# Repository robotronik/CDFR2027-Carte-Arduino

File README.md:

# CDFR2027-Carte-Arduino
La carte Arduino Controle de moteur pour CDFR 2027

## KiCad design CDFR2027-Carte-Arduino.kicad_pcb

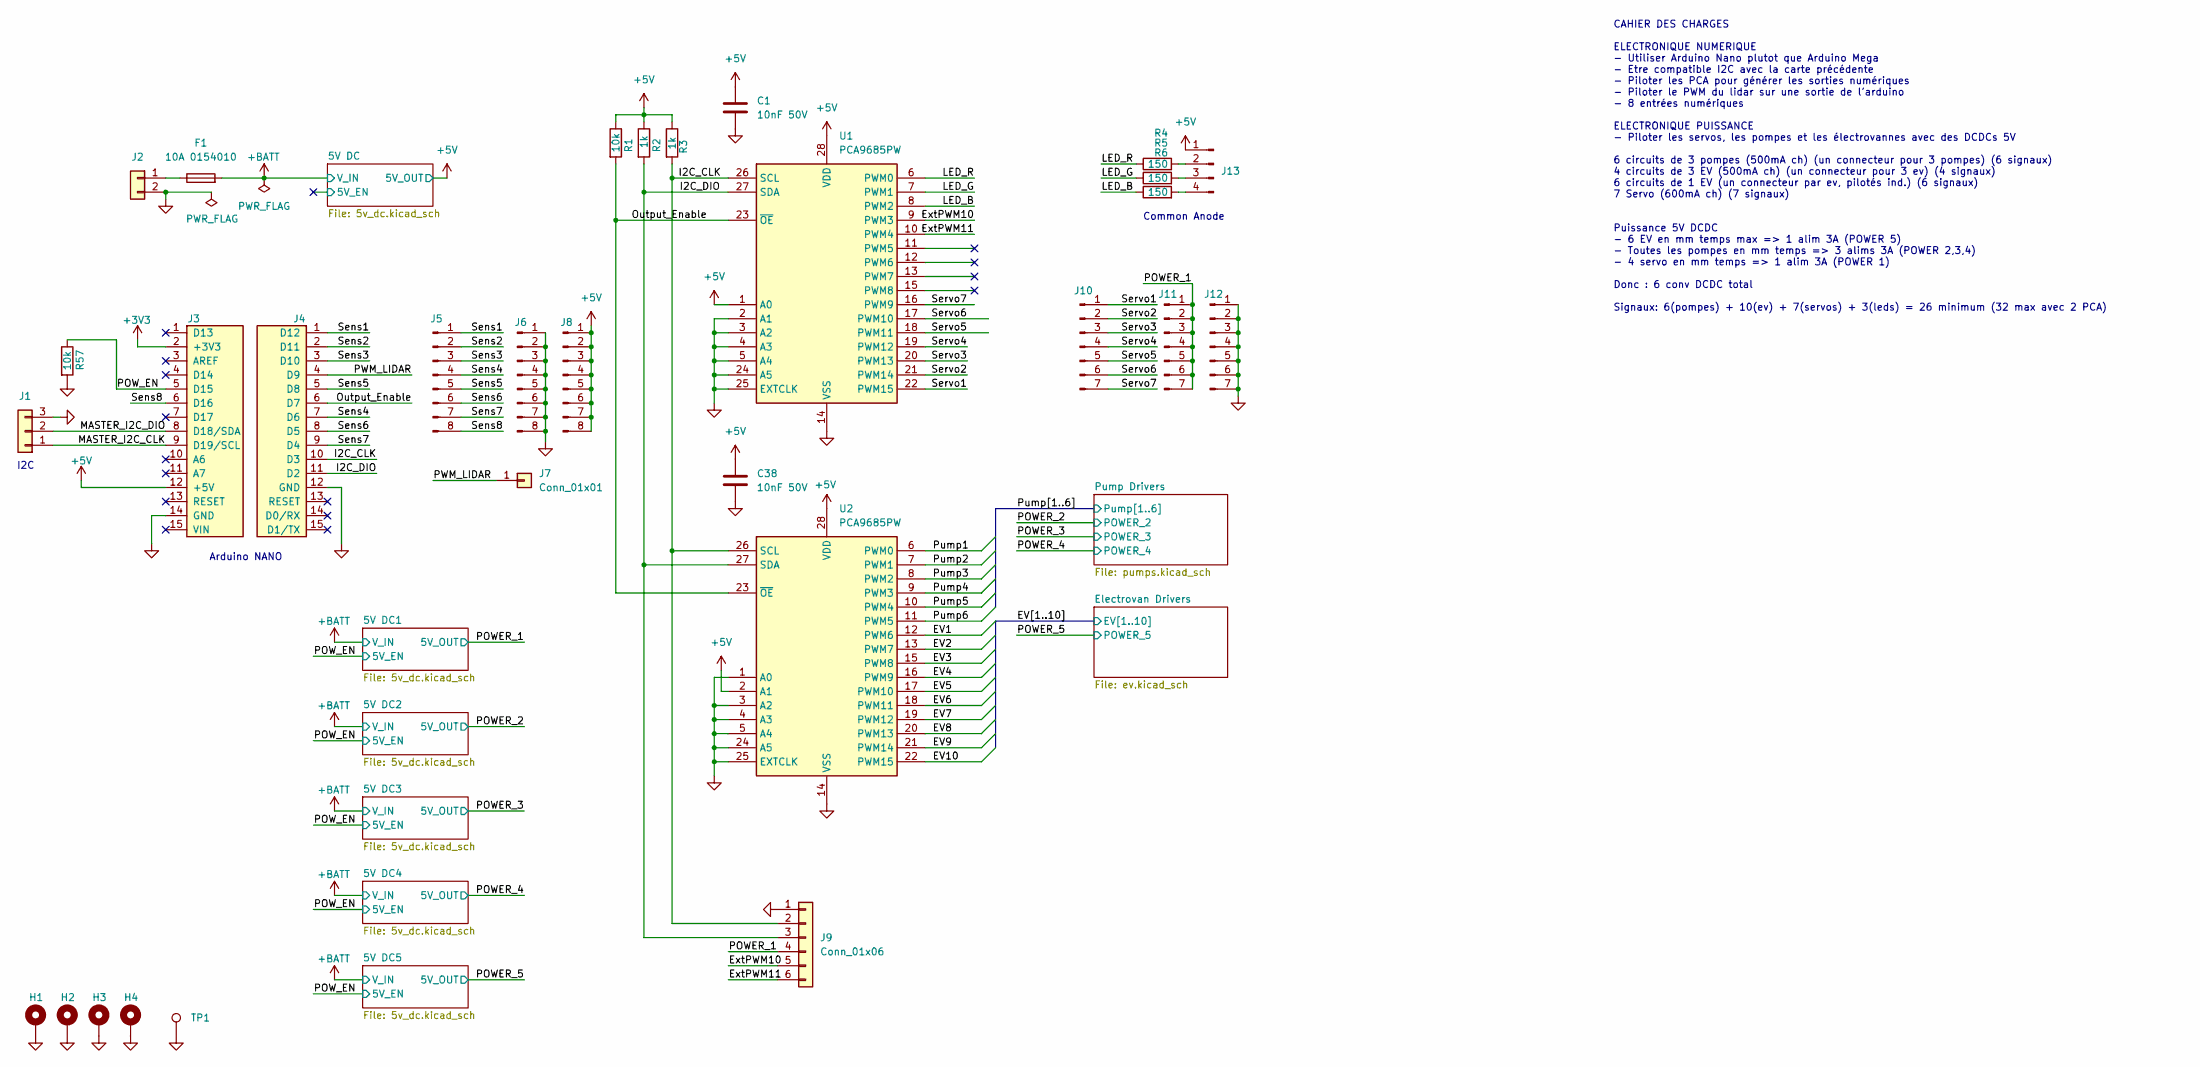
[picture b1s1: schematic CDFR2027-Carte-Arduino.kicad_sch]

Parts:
C1, C38: 10nF 50V; C_0805_2012Metric_Pad1.18x1.45mm_HandSolder; JLCPCB Part # C1710
F1: 10A 0154010; FUSE_0154004.DR; JLCPCB Part # C206921
H1, H2, H3, H4: MountingHole_Pad; MountingHole_3.2mm_M3_Pad_Via
J1: Conn_01x03; JST_XH_B3B-XH-A_1x03_P2.50mm_Vertical
J2: Conn_01x02; CUI_TBP01R1-508-02BE
J3: Analog; PinHeader_1x15_P2.54mm_Vertical
J4: Digital; PinHeader_1x15_P2.54mm_Vertical
J5, J6, J8: Conn_01x08_Pin; PinHeader_1x08_P2.54mm_Vertical
J7: Conn_01x01; PinHeader_1x01_P2.54mm_Vertical
J9: Conn_01x06; PinHeader_1x06_P2.54mm_Vertical
J10, J11, J12: Conn_01x07_Pin; PinHeader_1x07_P2.54mm_Vertical
J13: Conn_01x04_Pin; PinHeader_1x04_P2.54mm_Vertical
R1, R57: 10k; R_0805_2012Metric_Pad1.20x1.40mm_HandSolder; JLCPCB Part # C17414
R2, R3: 1k; R_0805_2012Metric_Pad1.20x1.40mm_HandSolder; JLCPCB Part # C17513
R4, R5, R6: 150; R_0805_2012Metric_Pad1.20x1.40mm_HandSolder; JLCPCB Part # C17471
TP1: TestPoint; TestPoint_Bridge_Pitch2.0mm_Drill0.7mm
U1, U2: PCA9685PW; TSSOP-28_4.4x9.7mm_P0.65mm; JLCPCB Part # C2678753

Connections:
+3V3: J3.2 (+3V3)
+5V: C1.1, C38.1, J3.12 (+5V), J8.1, J8.2, J8.3, J8.4, J8.5, J8.6, J8.7, J8.8, J13.1, R1.1, R2.1, R3.1, U1.1 (A0), U1.28 (VDD), U2.2 (A1), U2.28 (VDD); also elsewhere on the board
+BATT: F1.2; also elsewhere on the board
/EV1: U2.12 (PWM6); also elsewhere on the board
/EV2: U2.13 (PWM7); also elsewhere on the board
/EV3: U2.15 (PWM8); also elsewhere on the board
/EV4: U2.16 (PWM9); also elsewhere on the board
/EV5: U2.17 (PWM10); also elsewhere on the board
/EV6: U2.18 (PWM11); also elsewhere on the board
/EV7: U2.19 (PWM12); also elsewhere on the board
/EV8: U2.20 (PWM13); also elsewhere on the board
/EV9: U2.21 (PWM14); also elsewhere on the board
/EV10: U2.22 (PWM15); also elsewhere on the board
/ExtPWM10: J9.5, U1.9 (PWM3)
/ExtPWM11: J9.6, U1.10 (PWM4)
/I2C_CLK: J4.10 (D3), J9.2, R3.2, U1.26 (SCL), U2.26 (SCL)
/I2C_DIO: J4.11 (D2), J9.3, R2.2, U1.27 (SDA), U2.27 (SDA)
/LED_B: R6.1, U1.8 (PWM2)
/LED_G: R5.1, U1.7 (PWM1)
/LED_R: R4.1, U1.6 (PWM0)
/MASTER_I2C_CLK: J1.1, J3.9 (D19/SCL)
/MASTER_I2C_DIO: J1.2, J3.8 (D18/SDA)
/Output_Enable: J4.6 (D7), R1.2, U1.23 (~OE), U2.23 (~OE)
/POWER_1: J9.4, J11.1, J11.2, J11.3, J11.4, J11.5, J11.6, J11.7; also elsewhere on the board
/POW_EN: J3.5 (D15), R57.1; also elsewhere on the board
/PWM_LIDAR: J4.4 (D9), J7.1 (Pin_1_1)
/Pump1: U2.6 (PWM0); also elsewhere on the board
/Pump2: U2.7 (PWM1); also elsewhere on the board
/Pump3: U2.8 (PWM2); also elsewhere on the board
/Pump4: U2.9 (PWM3); also elsewhere on the board
/Pump5: U2.10 (PWM4); also elsewhere on the board
/Pump6: U2.11 (PWM5); also elsewhere on the board
/Sens1: J4.1 (D12), J5.1
/Sens2: J4.2 (D11), J5.2
/Sens3: J4.3 (D10), J5.3
/Sens4: J4.7 (D6), J5.4
/Sens5: J4.5 (D8), J5.5
/Sens6: J4.8 (D5), J5.6
/Sens7: J4.9 (D4), J5.7
/Sens8: J3.6 (D16), J5.8
/Servo1: J10.1, U1.22 (PWM15)
/Servo2: J10.2, U1.21 (PWM14)
/Servo3: J10.3, U1.20 (PWM13)
/Servo4: J10.4, U1.19 (PWM12)
/Servo5: J10.5, U1.18 (PWM11)
/Servo6: J10.6, U1.17 (PWM10)
/Servo7: J10.7, U1.16 (PWM9)
GND: C1.2, C38.2, H1.1 (1_1), H2.1 (1_1), H3.1 (1_1), H4.1 (1_1), J1.3, J2.2, J3.14 (GND), J4.12 (GND), J6.1, J6.2, J6.3, J6.4, J6.5, J6.6, J6.7, J6.8, J9.1, J12.1, J12.2, J12.3, J12.4, J12.5, J12.6, J12.7, R57.2, TP1.1 (1_1), U1.2 (A1), U1.3 (A2), U1.4 (A3), U1.5 (A4), U1.14 (VSS), U1.24 (A5), U1.25 (EXTCLK), U2.1 (A0), U2.3 (A2), U2.4 (A3), U2.5 (A4), U2.14 (VSS), U2.24 (A5), U2.25 (EXTCLK); also elsewhere on the board
unnamed: F1.1, J2.1
unnamed: J13.2, R4.2
unnamed: J13.3, R5.2
unnamed: J13.4, R6.2

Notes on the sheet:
I2C
Arduino NANO
Common Anode
CAHIER DES CHARGES ELECTRONIQUE NUMERIQUE - Utiliser Arduino Nano plutot que Arduino Mega - Etre compatible I2C avec la carte précédente - Piloter les PCA pour générer les sorties numériques - Piloter le PWM du lidar sur une sortie de l'arduino - 8 entrées numériques ELECTRONIQUE PUISSANCE - Pilote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

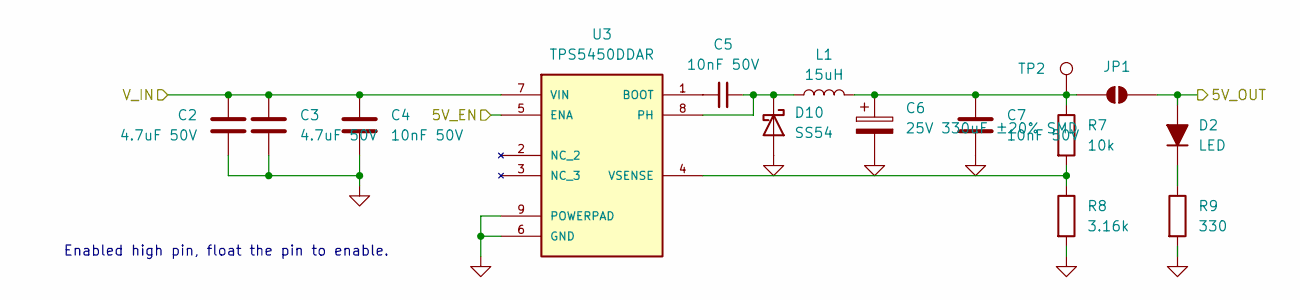
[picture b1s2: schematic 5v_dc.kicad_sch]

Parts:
C2, C3: 4.7uF 50V; C_0805_2012Metric_Pad1.18x1.45mm_HandSolder; JLCPCB Part # C437557
C4, C5, C7: 10nF 50V; C_0805_2012Metric_Pad1.18x1.45mm_HandSolder; JLCPCB Part # C1710
C6: 25V 330uF ±20% SMD; CP_Elec_8x10; JLCPCB Part # C127884
D2: LED; D_0805_2012Metric_Pad1.15x1.40mm_HandSolder; JLCPCB Part # C2297
D10: SS54; D_SMA; JLCPCB Part # C22452
JP1: SolderJumper_2_Open; SolderJumper-2_P1.3mm_Open_RoundedPad1.0x1.5mm
L1: 15uH; L_12x12mm_H8mm; JLCPCB Part # C40000
R7: 10k; R_0805_2012Metric_Pad1.20x1.40mm_HandSolder; JLCPCB Part # C17414
R8: 3.16k; R_0805_2012Metric_Pad1.20x1.40mm_HandSolder; JLCPCB Part # C2933413
R9: 330; R_0805_2012Metric_Pad1.20x1.40mm_HandSolder; JLCPCB Part # C17630
TP2: TestPoint; TestPoint_THTPad_D2.0mm_Drill1.0mm
U3: TPS5450DDAR; CONV_TPS5450DDAR; JLCPCB Part # C114425

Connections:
+5V: D2.2 (A), JP1.2 (B); also elsewhere on the board
+BATT: C2.2, C3.1, C4.1, U3.7 (VIN); also elsewhere on the board
/5V DC/5V_EN: U3.5 (ENA)
GND: C2.1, C3.2, C4.2, C6.2, C7.2, D10.2 (A), R8.2, R9.2, U3.6 (GND), U3.9 (POWERPAD); also elsewhere on the board
unnamed: D2.1 (K), R9.1
unnamed: C5.2, D10.1 (K), L1.1, U3.8 (PH)
unnamed: C6.1, C7.1, JP1.1 (A), L1.2, R7.1, TP2.1 (1_1)
unnamed: C5.1, U3.1 (BOOT)
unnamed: R7.2, R8.1, U3.4 (VSENSE)

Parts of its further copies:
C8, C9, C14, C15, C20, C21, C26, C27, C32, C33: 4.7uF 50V; C_0805_2012Metric_Pad1.18x1.45mm_HandSolder; JLCPCB Part # C437557
C10, C11, C13, C16, C17, C19, C22, C23, C25, C28, C29, C31, C34, C35, C37: 10nF 50V; C_0805_2012Metric_Pad1.18x1.45mm_HandSolder; JLCPCB Part # C1710
C12, C18, C24, C30, C36: 25V 330uF ±20% SMD; CP_Elec_8x10; JLCPCB Part # C127884
D4, D6, D8, D11, D13: LED; D_0805_2012Metric_Pad1.15x1.40mm_HandSolder; JLCPCB Part # C2297
D12, D29, D30, D31, D32: SS54; D_SMA; JLCPCB Part # C22452
JP2, JP3, JP4, JP5, JP6: SolderJumper_2_Open; SolderJumper-2_P1.3mm_Open_RoundedPad1.0x1.5mm
L2, L3, L4, L5, L6: 15uH; L_12x12mm_H8mm; JLCPCB Part # C40000
R10, R13, R16, R21, R24: 10k; R_0805_2012Metric_Pad1.20x1.40mm_HandSolder; JLCPCB Part # C17414
R11, R14, R17, R22, R25: 3.16k; R_0805_2012Metric_Pad1.20x1.40mm_HandSolder; JLCPCB Part # C2933413
R12, R15, R18, R23, R26: 330; R_0805_2012Metric_Pad1.20x1.40mm_HandSolder; JLCPCB Part # C17630
TP3, TP4, TP5, TP6, TP7: TestPoint; TestPoint_THTPad_D2.0mm_Drill1.0mm
U4, U5, U6, U7, U8: TPS5450DDAR; CONV_TPS5450DDAR; JLCPCB Part # C114425

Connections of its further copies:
+BATT: C8.2, C9.1, C10.1, C14.2, C15.1, C16.1, C20.2, C21.1, C22.1, C26.2, C27.1, C28.1, C32.2, C33.1, C34.1, U4.7 (VIN), U5.7 (VIN), U6.7 (VIN), U7.7 (VIN), U8.7 (VIN); also elsewhere on the board
/POWER_1: D4.2 (A), JP2.2 (B); also elsewhere on the board
/POWER_2: D6.2 (A), JP3.2 (B); also elsewhere on the board
/POWER_3: D8.2 (A), JP4.2 (B); also elsewhere on the board
/POWER_4: D11.2 (A), JP5.2 (B); also elsewhere on the board
/POWER_5: D13.2 (A), JP6.2 (B); also elsewhere on the board
/POW_EN: U4.5 (ENA), U5.5 (ENA), U6.5 (ENA), U7.5 (ENA), U8.5 (ENA); also elsewhere on the board
GND: C8.1, C9.2, C10.2, C12.2, C13.2, C14.1, C15.2, C16.2, C18.2, C19.2, C20.1, C21.2, C22.2, C24.2, C25.2, C26.1, C27.2, C28.2, C30.2, C31.2, C32.1, C33.2, C34.2, C36.2, C37.2, D12.2 (A), D29.2 (A), D30.2 (A), D31.2 (A), D32.2 (A), R11.2, R12.2, R14.2, R15.2, R17.2, R18.2, R22.2, R23.2, R25.2, R26.2, U4.6 (GND), U4.9 (POWERPAD), U5.6 (GND), U5.9 (POWERPAD), U6.6 (GND), U6.9 (POWERPAD), U7.6 (GND), U7.9 (POWERPAD), U8.6 (GND), U8.9 (POWERPAD); also elsewhere on the board
unnamed: D4.1 (K), R12.1
unnamed: D6.1 (K), R15.1
unnamed: D8.1 (K), R18.1
unnamed: D11.1 (K), R23.1
unnamed: C11.2, D12.1 (K), L2.1, U4.8 (PH)
unnamed: D13.1 (K), R26.1
unnamed: C17.2, D29.1 (K), L3.1, U5.8 (PH)
unnamed: C23.2, D30.1 (K), L4.1, U6.8 (PH)
unnamed: C29.2, D31.1 (K), L5.1, U7.8 (PH)
unnamed: C35.2, D32.1 (K), L6.1, U8.8 (PH)
unnamed: C12.1, C13.1, JP2.1 (A), L2.2, R10.1, TP3.1 (1_1)
unnamed: C18.1, C19.1, JP3.1 (A), L3.2, R13.1, TP4.1 (1_1)
unnamed: C24.1, C25.1, JP4.1 (A), L4.2, R16.1, TP5.1 (1_1)
unnamed: C30.1, C31.1, JP5.1 (A), L5.2, R21.1, TP6.1 (1_1)
unnamed: C36.1, C37.1, JP6.1 (A), L6.2, R24.1, TP7.1 (1_1)
unnamed: C11.1, U4.1 (BOOT)
unnamed: R10.2, R11.1, U4.4 (VSENSE)
unnamed: C17.1, U5.1 (BOOT)
unnamed: R13.2, R14.1, U5.4 (VSENSE)
unnamed: C23.1, U6.1 (BOOT)
unnamed: R16.2, R17.1, U6.4 (VSENSE)
unnamed: C29.1, U7.1 (BOOT)
unnamed: R21.2, R22.1, U7.4 (VSENSE)
unnamed: C35.1, U8.1 (BOOT)
unnamed: R24.2, R25.1, U8.4 (VSENSE)

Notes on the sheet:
Enabled high pin, float the pin to enable.

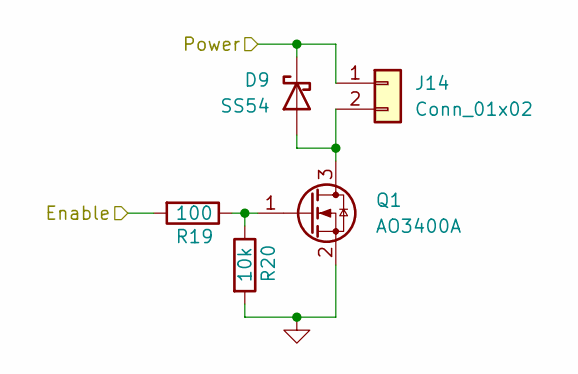
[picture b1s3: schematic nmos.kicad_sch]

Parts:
D9: SS54; D_SMA; JLCPCB Part # C22452
J14: Conn_01x02; JST_XH_B2B-XH-A_1x02_P2.50mm_Vertical
Q1: AO3400A; SOT-23; JLCPCB Part # C20917
R19: 100; R_0805_2012Metric_Pad1.20x1.40mm_HandSolder; JLCPCB Part # C17408
R20: 10k; R_0805_2012Metric_Pad1.20x1.40mm_HandSolder; JLCPCB Part # C17414

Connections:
/POWER_2: D9.1 (K), J14.1; also elsewhere on the board
/Pump1: R19.2; also elsewhere on the board
GND: Q1.2 (S), R20.2; also elsewhere on the board
unnamed: D9.2 (A), J14.2, Q1.3 (D)
unnamed: Q1.1 (G), R19.1, R20.1

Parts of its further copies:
D14, D15, D16, D17, D18, D19, D20, D21, D22, D23, D24, D25, D26, D27, D28: SS54; D_SMA; JLCPCB Part # C22452
J15, J16, J17, J18, J19, J20, J21, J22, J23, J24, J25, J26, J27, J28, J29: Conn_01x02; JST_XH_B2B-XH-A_1x02_P2.50mm_Vertical
Q2, Q3, Q4, Q5, Q6, Q7, Q8, Q9, Q10, Q11, Q12, Q13, Q14, Q15, Q16: AO3400A; SOT-23; JLCPCB Part # C20917
R27, R29, R31, R33, R35, R37, R39, R41, R43, R45, R47, R49, R51, R53, R55: 100; R_0805_2012Metric_Pad1.20x1.40mm_HandSolder; JLCPCB Part # C17408
R28, R30, R32, R34, R36, R38, R40, R42, R44, R46, R48, R50, R52, R54, R56: 10k; R_0805_2012Metric_Pad1.20x1.40mm_HandSolder; JLCPCB Part # C17414

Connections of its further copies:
/EV1: R37.2; also elsewhere on the board
/EV2: R39.2; also elsewhere on the board
/EV3: R41.2; also elsewhere on the board
/EV4: R43.2; also elsewhere on the board
/EV5: R45.2; also elsewhere on the board
/EV6: R47.2; also elsewhere on the board
/EV7: R49.2; also elsewhere on the board
/EV8: R51.2; also elsewhere on the board
/EV9: R53.2; also elsewhere on the board
/EV10: R55.2; also elsewhere on the board
/POWER_2: D14.1 (K), J15.1; also elsewhere on the board
/POWER_3: D15.1 (K), D16.1 (K), J16.1, J17.1; also elsewhere on the board
/POWER_4: D17.1 (K), D18.1 (K), J18.1, J19.1; also elsewhere on the board
/POWER_5: D19.1 (K), D20.1 (K), D21.1 (K), D22.1 (K), D23.1 (K), D24.1 (K), D25.1 (K), D26.1 (K), D27.1 (K), D28.1 (K), J20.1, J21.1, J22.1, J23.1, J24.1, J25.1, J26.1, J27.1, J28.1, J29.1; also elsewhere on the board
/Pump2: R27.2; also elsewhere on the board
/Pump3: R29.2; also elsewhere on the board
/Pump4: R31.2; also elsewhere on the board
/Pump5: R33.2; also elsewhere on the board
/Pump6: R35.2; also elsewhere on the board
GND: Q2.2 (S), Q3.2 (S), Q4.2 (S), Q5.2 (S), Q6.2 (S), Q7.2 (S), Q8.2 (S), Q9.2 (S), Q10.2 (S), Q11.2 (S), Q12.2 (S), Q13.2 (S), Q14.2 (S), Q15.2 (S), Q16.2 (S), R28.2, R30.2, R32.2, R34.2, R36.2, R38.2, R40.2, R42.2, R44.2, R46.2, R48.2, R50.2, R52.2, R54.2, R56.2; also elsewhere on the board
unnamed: D14.2 (A), J15.2, Q2.3 (D)
unnamed: D15.2 (A), J16.2, Q3.3 (D)
unnamed: D16.2 (A), J17.2, Q4.3 (D)
unnamed: D17.2 (A), J18.2, Q5.3 (D)
unnamed: D18.2 (A), J19.2, Q6.3 (D)
unnamed: D19.2 (A), J20.2, Q7.3 (D)
unnamed: D20.2 (A), J21.2, Q8.3 (D)
unnamed: D21.2 (A), J22.2, Q9.3 (D)
unnamed: D22.2 (A), J23.2, Q10.3 (D)
unnamed: D23.2 (A), J24.2, Q11.3 (D)
unnamed: D24.2 (A), J25.2, Q12.3 (D)
unnamed: D25.2 (A), J26.2, Q13.3 (D)
unnamed: D26.2 (A), J27.2, Q14.3 (D)
unnamed: D27.2 (A), J28.2, Q15.3 (D)
unnamed: D28.2 (A), J29.2, Q16.3 (D)
unnamed: Q2.1 (G), R27.1, R28.1
unnamed: Q3.1 (G), R29.1, R30.1
unnamed: Q4.1 (G), R31.1, R32.1
unnamed: Q5.1 (G), R33.1, R34.1
unnamed: Q6.1 (G), R35.1, R36.1
unnamed: Q7.1 (G), R37.1, R38.1
unnamed: Q8.1 (G), R39.1, R40.1
unnamed: Q9.1 (G), R41.1, R42.1
unnamed: Q10.1 (G), R43.1, R44.1
unnamed: Q11.1 (G), R45.1, R46.1
unnamed: Q12.1 (G), R47.1, R48.1
unnamed: Q13.1 (G), R49.1, R50.1
unnamed: Q14.1 (G), R51.1, R52.1
unnamed: Q15.1 (G), R53.1, R54.1
unnamed: Q16.1 (G), R55.1, R56.1

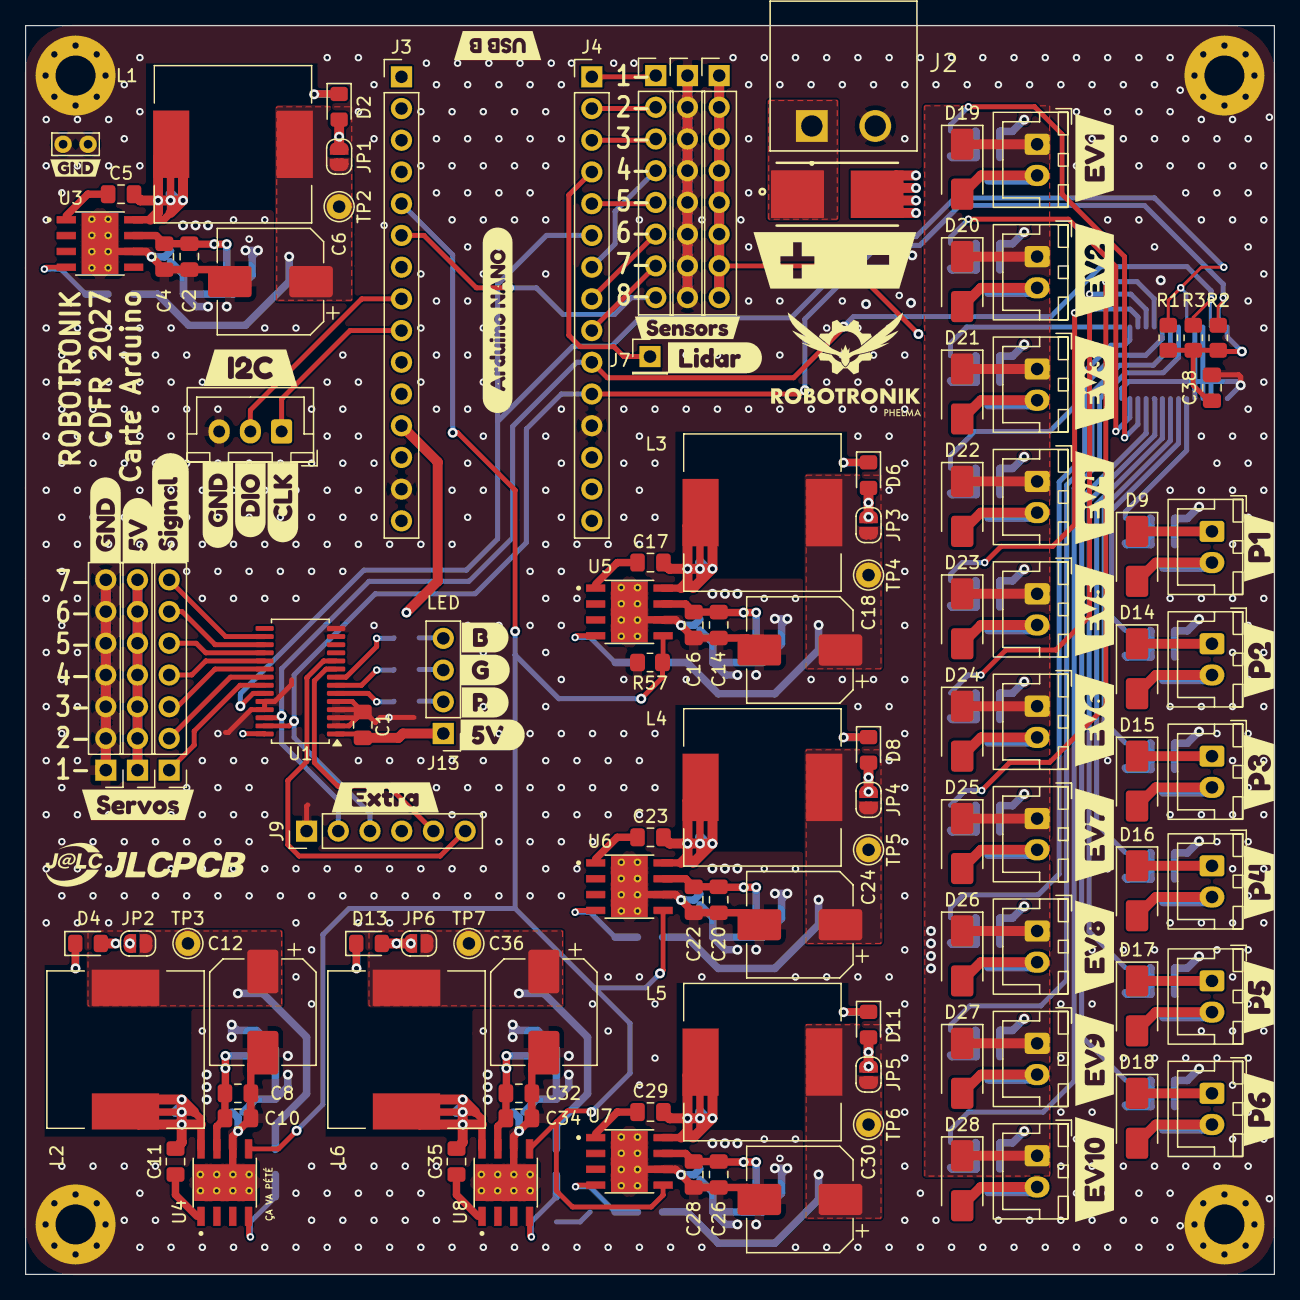
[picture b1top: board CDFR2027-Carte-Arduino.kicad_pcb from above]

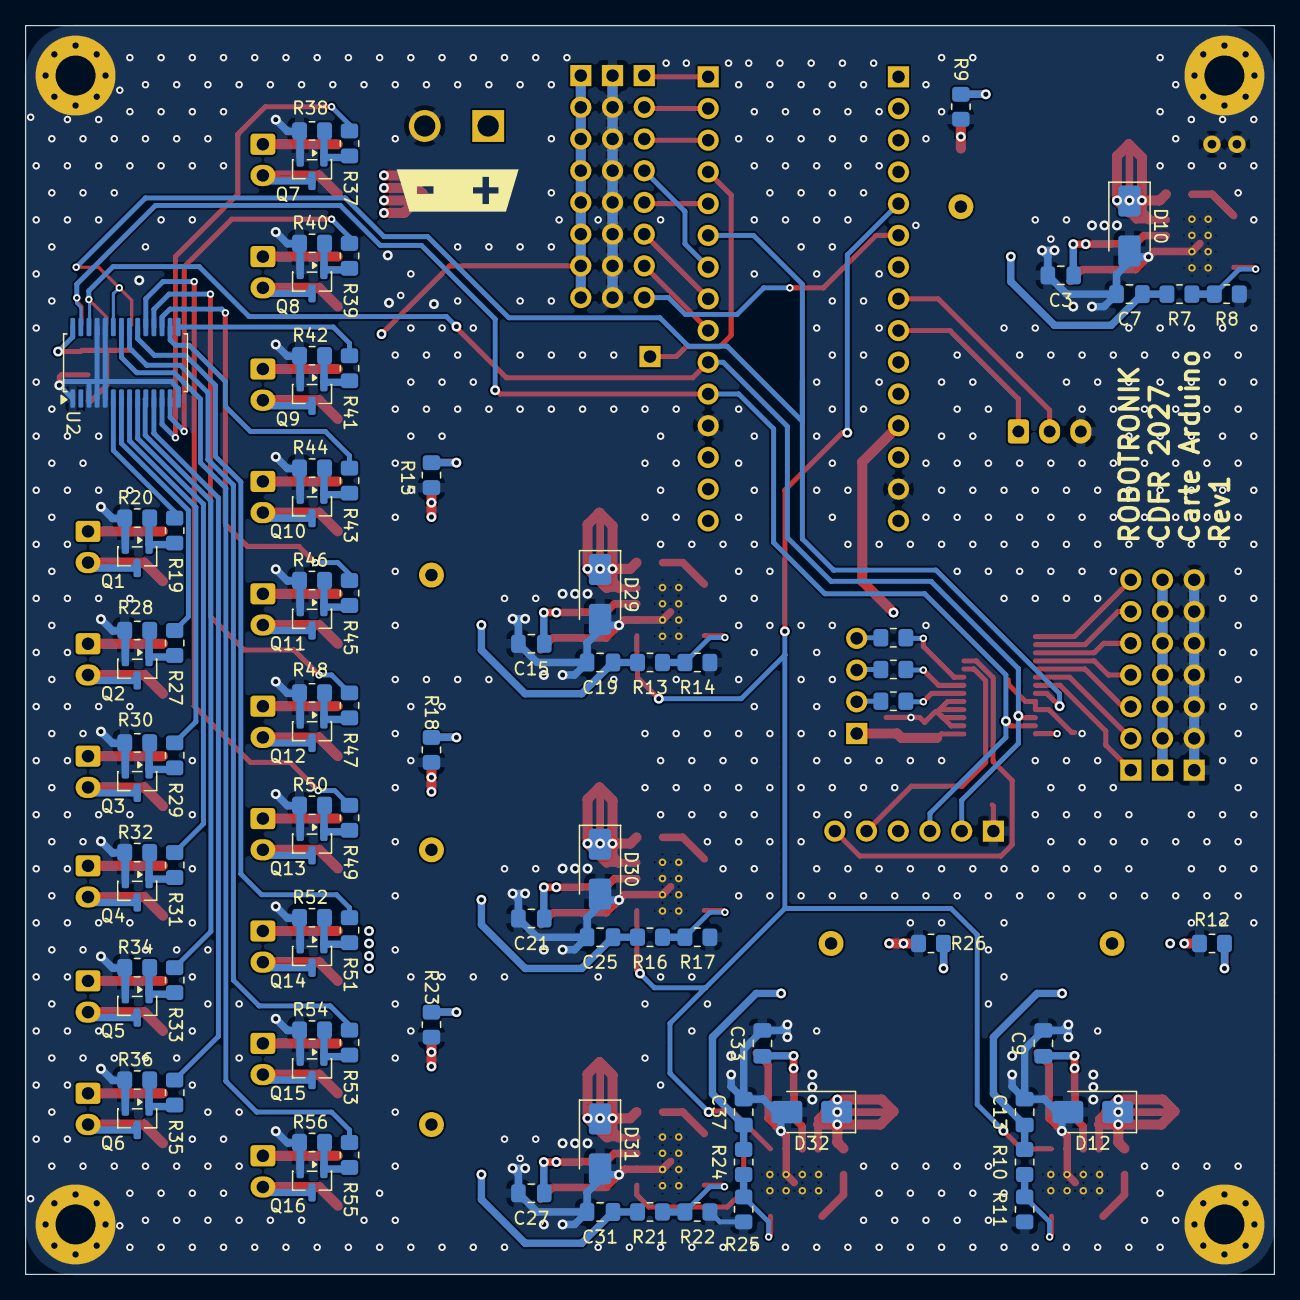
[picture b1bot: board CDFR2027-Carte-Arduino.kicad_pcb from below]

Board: 4 copper layers, 100.0 x 100.0 mm, 238 parts (89 on the bottom side), 117 nets.

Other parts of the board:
LOGO1: LOGO_Robotronik
LOGO2: LOGO_JLCPCB
kibuzzard-6B061A60: G***; kibuzzard-6B061A60
kibuzzard-6B061A66: G***; kibuzzard-6B061A66
kibuzzard-6B061A70: G***; kibuzzard-6B061A70
kibuzzard-6B061A73: G***; kibuzzard-6B061A73
kibuzzard-6B061AA9: G***; kibuzzard-6B061AA9
kibuzzard-6B0615CA: G***; kibuzzard-6B0615CA
kibuzzard-6B0616AE: G***; kibuzzard-6B0616AE
kibuzzard-6B0616D5: G***; kibuzzard-6B0616D5
kibuzzard-6B0616DA: G***; kibuzzard-6B0616DA
kibuzzard-6B0616DF: G***; kibuzzard-6B0616DF
kibuzzard-6B0616E4: G***; kibuzzard-6B0616E4
kibuzzard-6B0616E8: G***; kibuzzard-6B0616E8
kibuzzard-6B0617C5: G***; kibuzzard-6B0617C5
kibuzzard-6B0619A4: G***; kibuzzard-6B0619A4
kibuzzard-6B0619CE: G***; kibuzzard-6B0619CE
kibuzzard-6B0619D6: G***; kibuzzard-6B0619D6
kibuzzard-6B0619FE: G***; kibuzzard-6B0619FE
kibuzzard-6B06160D: G***; kibuzzard-6B06160D
kibuzzard-6B06161C: G***; kibuzzard-6B06161C
kibuzzard-6B06162B: G***; kibuzzard-6B06162B
kibuzzard-6B06162F: G***; kibuzzard-6B06162F
kibuzzard-6B06176C: G***; kibuzzard-6B06176C
kibuzzard-6B06179C: G***; kibuzzard-6B06179C
kibuzzard-6B06185A: G***; kibuzzard-6B06185A
kibuzzard-6B06186F: G***; kibuzzard-6B06186F
kibuzzard-6B06188A: G***; kibuzzard-6B06188A
kibuzzard-6B061272: G***; kibuzzard-6B061272
kibuzzard-6B061287: G***; kibuzzard-6B061287
kibuzzard-6B061619: G***; kibuzzard-6B061619
kibuzzard-6B061621: G***; kibuzzard-6B061621
kibuzzard-6B061624: G***; kibuzzard-6B061624
kibuzzard-6B061628: G***; kibuzzard-6B061628
kibuzzard-6B061633: G***; kibuzzard-6B061633
kibuzzard-6B061847: G***; kibuzzard-6B061847
kibuzzard-6B061951: G***; kibuzzard-6B061951
kibuzzard-6B061989: G***; kibuzzard-6B061989

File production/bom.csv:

Designator,Footprint,Quantity,Value,LCSC Part #
"C1, C10, C11, C13, C16, C17, C19, C22, C23, C25, C28, C29, C31, C34, C35, C37, C38, C4, C5, C7",0805,20,10nF 50V,C1710
"C12, C18, C24, C30, C36, C6",CP_Elec_8x10,6,25V 330uF ±20% SMD,C127884
"C14, C15, C2, C20, C21, C26, C27, C3, C32, C33, C8, C9",0805,12,4.7uF 50V,C437557
"D10, D12, D14, D15, D16, D17, D18, D19, D20, D21, D22, D23, D24, D25, D26, D27, D28, D29, D30, D31, D32, D9",D_SMA,22,SS54,C22452
"D11, D13, D2, D4, D6, D8",0805,6,LED,C2297
F1,FUSE_0154004.DR,1,10A 0154010,C206921
"L1, L2, L3, L4, L5, L6",L_12x12mm_H8mm,6,15uH,C40000
"Q1, Q10, Q11, Q12, Q13, Q14, Q15, Q16, Q2, Q3, Q4, Q5, Q6, Q7, Q8, Q9",SOT-23,16,AO3400A,C20917
"R1, R10, R13, R16, R20, R21, R24, R28, R30, R32, R34, R36, R38, R40, R42, R44, R46, R48, R50, R52, R54, R56, R57, R7",0805,24,10k,C17414
"R11, R14, R17, R22, R25, R8",0805,6,3.16k,C2933413
"R12, R15, R18, R23, R26, R9",0805,6,330,C17630
"R19, R27, R29, R31, R33, R35, R37, R39, R41, R43, R45, R47, R49, R51, R53, R55",0805,16,100,C17408
"R2, R3",0805,2,1k,C17513
"R4, R5, R6",0805,3,150,C17471
"U1, U2",TSSOP-28_4.4x9.7mm_P0.65mm,2,PCA9685PW,C2678753
"U3, U4, U5, U6, U7, U8",CONV_TPS5450DDAR,6,TPS5450DDAR,C114425
